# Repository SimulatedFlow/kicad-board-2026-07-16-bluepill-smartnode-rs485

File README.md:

# 2026-07-16-bluepill-smartnode-rs485

<!-- SF-STORE-BLOCK:BEGIN -->
## 🛒 Source-available — see before you buy

This repository contains the **full design files** of a commercial hardware board. It is **source-available, not open source**: read it, evaluate it, then buy a license to use it. See **LICENSE.md (source-available, purchase required)**.

**Get it / Buy:**
- **Order on eBay** (this board, bare PCB): https://www.ebay.de/itm/398222427962
- Product page (specs, photos, price): https://simulatedflow.teufel-engineering.com/platinen/2026-07-16-bluepill-smartnode-rs485/
- eBay store — all our boards and PCB art: https://www.ebay.de/usr/simula-9
- Merch shop (dev & gaming): https://simulatedflow.myspreadshop.de
- Merch shop (Synthetica / EDM): https://synthetica.myspreadshop.de
- Direct / invoice (Simulated Flow UG): simulatedflow@gmail.com

### 📬 **Free Board Documentation & Firmware Pack**

Schematics, BOMs and example-firmware docs for our STM32 carrier boards. Get it by joining the newsletter — plus a heads-up when something new ships. Double opt-in, unsubscribe in one click, no address sharing.

👉 **[Get the free pack](https://simulatedflow.teufel-engineering.com/newsletter/hardware/?q=gh)**

_© 2026 Simulated Flow UG. All rights reserved._
<!-- SF-STORE-BLOCK:END -->

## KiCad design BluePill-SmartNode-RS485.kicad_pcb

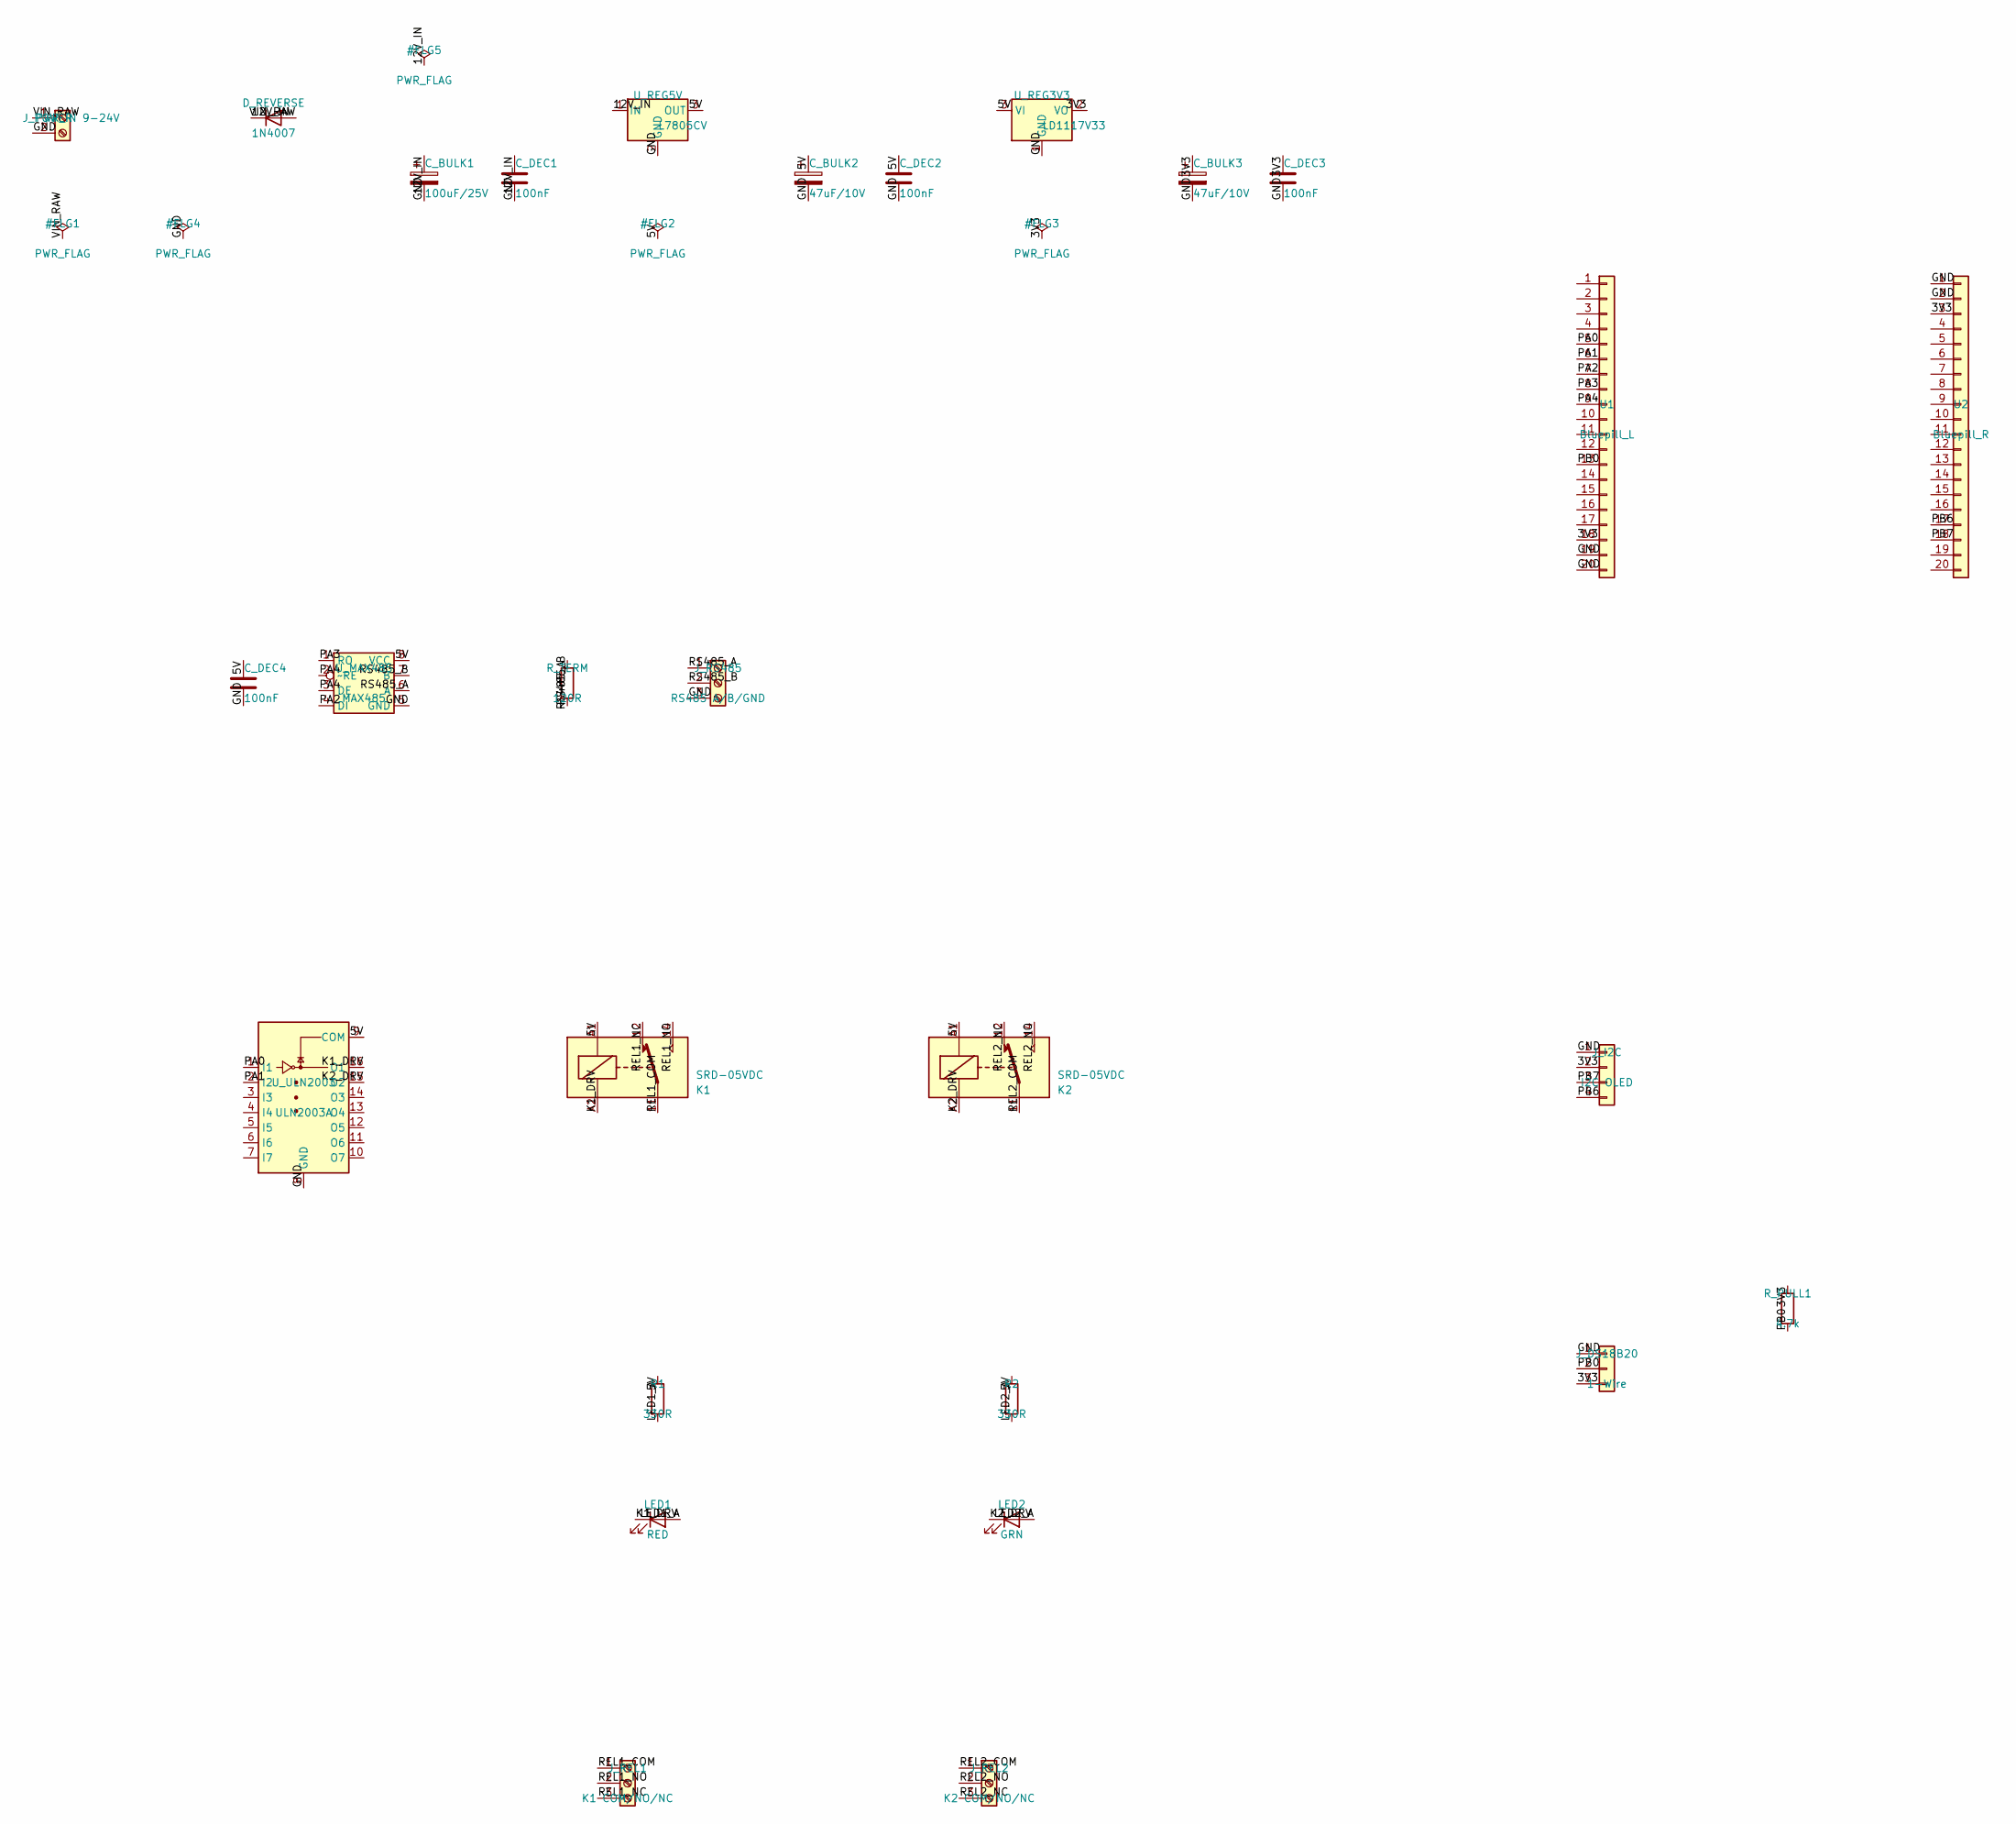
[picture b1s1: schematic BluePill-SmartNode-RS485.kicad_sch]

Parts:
C_BULK1: 100uF/25V; CP_Radial_D8.0mm_P3.50mm
C_BULK2, C_BULK3: 47uF/10V; CP_Radial_D5.0mm_P2.00mm
C_DEC1, C_DEC2, C_DEC3, C_DEC4: 100nF; C_Disc_D5.0mm_W2.5mm_P5.00mm
D_REVERSE: 1N4007; D_DO-41_SOD81_P10.16mm_Horizontal
J_DS18B20: 1-Wire; PinHeader_1x03_P2.54mm_Vertical
J_I2C: I2C OLED; PinHeader_1x04_P2.54mm_Vertical
J_POWER: PWR_IN 9-24V; TerminalBlock_Phoenix_MKDS-1,5-2-5.08_1x02_P5.08mm_Horizont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
J_REL1: K1 COM/NO/NC; TerminalBlock_Phoenix_MKDS-1,5-3-5.08_1x03_P5.08mm_Horizont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
J_REL2: K2 COM/NO/NC; TerminalBlock_Phoenix_MKDS-1,5-3-5.08_1x03_P5.08mm_Horizont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
J_RS485: RS485 A/B/GND; TerminalBlock_Phoenix_MKDS-1,5-3-5.08_1x03_P5.08mm_Horizont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
K1, K2: SRD-05VDC; Relay_SPDT_Hongfa_JQC-3FF_0XX-1Z
LED1: RED; LED_D5.0mm
LED2: GRN; LED_D5.0mm
R1, R2: 330R; R_Axial_DIN0207_L6.3mm_D2.5mm_P10.16mm_Horizontal
R_PULL1: 4.7k; R_Axial_DIN0207_L6.3mm_D2.5mm_P10.16mm_Horizontal
R_TERM: 120R; R_Axial_DIN0207_L6.3mm_D2.5mm_P10.16mm_Horizontal
U1: Bluepill_L; PinSocket_1x20_P2.54mm_Vertical
U2: Bluepill_R; PinSocket_1x20_P2.54mm_Vertical
U_MAX485: MAX485; DIP-8_W7.62mm
U_REG3V3: LD1117V33; TO-220-3_Vertical
U_REG5V: L7805CV; TO-220-3_Vertical
U_ULN2003: ULN2003A; DIP-16_W7.62mm

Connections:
3V3: C_BULK3.1, C_DEC3.1, J_DS18B20.3, J_I2C.2, R_PULL1.1, U1.18, U2.3, U_REG3V3.2 (VO)
5V: C_BULK2.1, C_DEC2.1, C_DEC4.1, K1.A1, K2.A1, R1.1, R2.1, U_MAX485.8 (VCC), U_REG3V3.3 (VI), U_REG5V.3 (OUT), U_ULN2003.9 (COM)
12V_IN: C_BULK1.1, C_DEC1.1, D_REVERSE.1 (K), U_REG5V.1 (IN)
GND: C_BULK1.2, C_BULK2.2, C_BULK3.2, C_DEC1.2, C_DEC2.2, C_DEC3.2, C_DEC4.2, J_DS18B20.1, J_I2C.1, J_POWER.2, J_RS485.3, U1.19, U1.20, U2.1, U2.2, U_MAX485.5 (GND), U_REG3V3.1 (GND), U_REG5V.2 (GND), U_ULN2003.8 (GND)
K1_DRV: K1.A2, LED1.1 (K), U_ULN2003.16 (O1)
K2_DRV: K2.A2, LED2.1 (K), U_ULN2003.15 (O2)
LED1_A: LED1.2 (A), R1.2
LED2_A: LED2.2 (A), R2.2
PA0: U1.5, U_ULN2003.1 (I1)
PA1: U1.6, U_ULN2003.2 (I2)
PA2: U1.7, U_MAX485.4 (DI)
PA3: U1.8, U_MAX485.1 (RO)
PA4: U1.9, U_MAX485.2 (~RE), U_MAX485.3 (DE)
PB0: J_DS18B20.2, R_PULL1.2, U1.13
PB6: J_I2C.4, U2.17
PB7: J_I2C.3, U2.18
REL1_COM: J_REL1.1, K1.11
REL1_NC: J_REL1.3, K1.12
REL1_NO: J_REL1.2, K1.14
REL2_COM: J_REL2.1, K2.11
REL2_NC: J_REL2.3, K2.12
REL2_NO: J_REL2.2, K2.14
RS485_A: J_RS485.1, R_TERM.1, U_MAX485.6 (A)
RS485_B: J_RS485.2, R_TERM.2, U_MAX485.7 (B)
VIN_RAW: D_REVERSE.2 (A), J_POWER.1

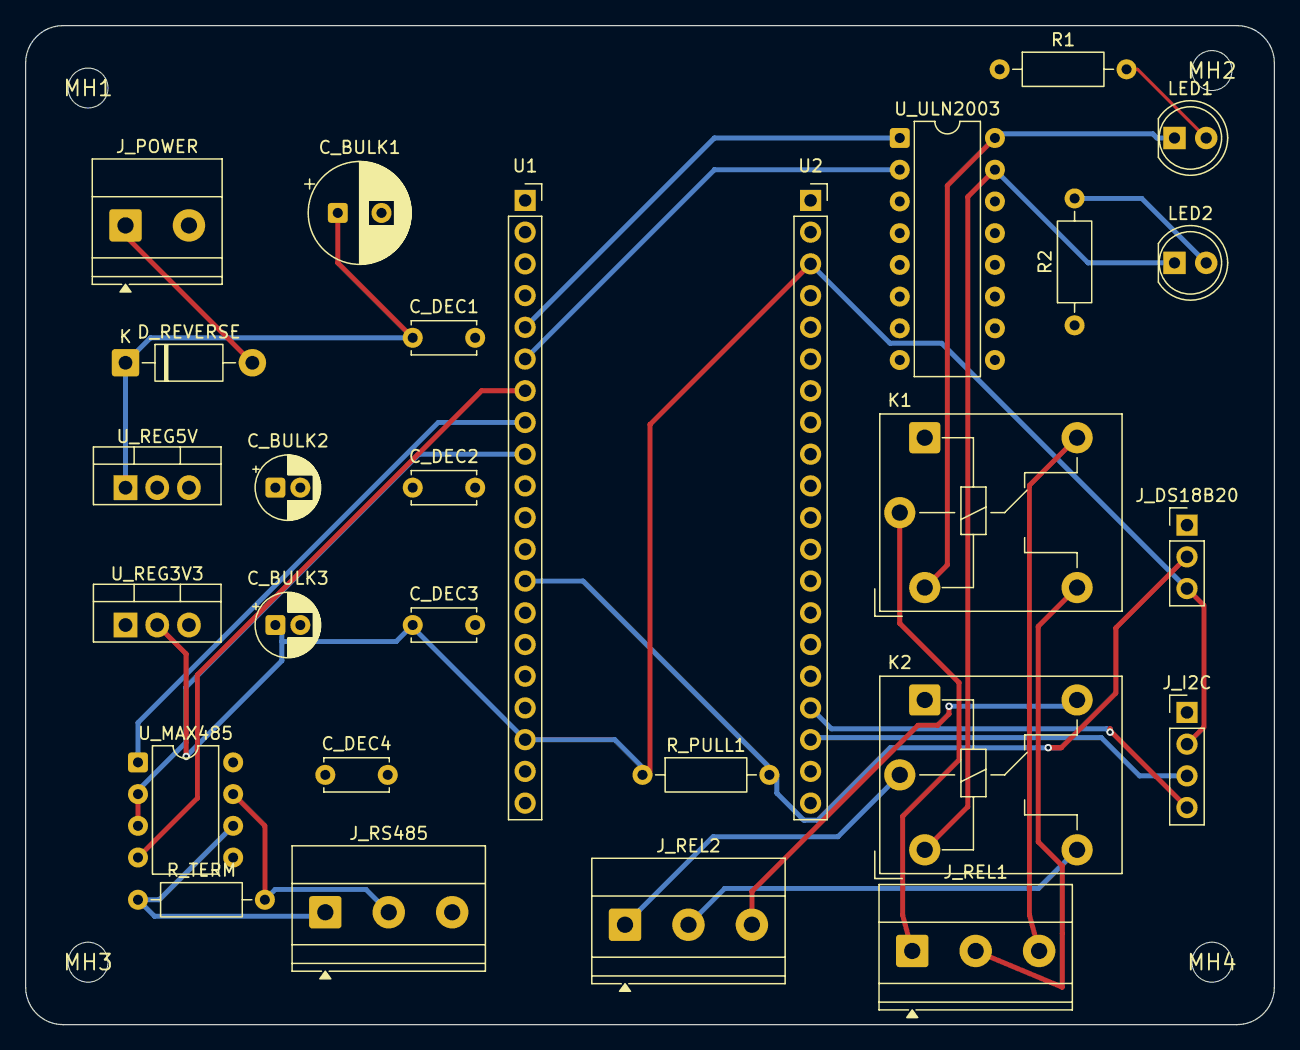
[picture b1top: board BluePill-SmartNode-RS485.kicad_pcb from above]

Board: 4 copper layers, 100.0 x 80.0 mm, 32 parts (0 on the bottom side), 25 nets.

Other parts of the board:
MH1, MH2, MH3, MH4: MountingHole_3.2mm
